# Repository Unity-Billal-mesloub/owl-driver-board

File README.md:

The OWL Driver Board is a solid-state relay HAT for the Raspberry Pi. It was
developed for use with the [Open Weed Locator](https://github.com/Unity-Agriculture/OpenWeedLocator) 
but is suitable for any high-power, industrial, automotive or agricultural application.

It allows a Raspberry Pi to drive either 4x or 16x 2A outputs in any 12V or 24V
system, with the solid state switching allowing PWM control, including for
dimming LED strips. Outputs can be placed in parallel for more power if needed.

It is able to tolerate high levels of electrical noise, reverse polarity, short
circuit conditions and over voltage. It also protects the Pi from all this
electrical nastiness and provides a filtered source of 5V @ 5A!

It's ideal for use safely driving LED strips, high power motors, relays and
solenoids from a Raspberry Pi.

The board aims to be difficult to misconfigure and hard to damage.
Self-resetting polyfuses on the input and outputs limit current, and
TVS+Schottky diodes provide reverse polarity protection, protection against
noise and inductive voltage spikes, and over-voltage protection. This
protection also extends to communication buses with the Raspberry Pi.

# Features

### Both models (4x and 16x output versions)

* Open Hardware, made in the UK: schematics and design files freely available.
* Working voltage 7-26V
* 4x or 16x fused outputs, each max. 2A, high-side switched
* 1x e-stop / global enable input
* Outputs can be driven in multiple ways, configurable by a header
* From Raspberry PI GPIOs
* Directly from external control, via wires to a header. Control inputs are tolerant up to 26V.
* Buck converter generates 5.1V @ 3A continuous / 5A burst to power the Raspberry Pi (Pi 5 compatible!)
* Input and outputs are fused, with protection against over-voltage, reverse polarity, and inductive spikes
* LED indication of blown fuses

### Additional features for the 4x output version only

* 1x fused input max. 7A
* Self-resetting input polyfuse
* Integrated PCA9685 PWM driver allows optional PWM control via I2C, compatible with Adafruit PCA9675 Python libraries
* Input and output connectors use high-quality Phoenix Contact screw terminals
* Version 2.4

### Additional features for the 16x output version only

* 3x fused inputs max. 10A each (connect all inputs in parallel for 30A total board input power)
* 10A mini-blade fuses on inputs
* Spare fuse holder
* Inputs and outputs use JST VH connectors
* Version 1.0

# Purchase a finished board

You can buy a finished board (4x or 16x output versions) via the following distributors:

 * [paradar.co.uk](https://paradar.co.uk/products/owl-driver-board-raspberry-pi-automotive-relay-hat)

# Changelog

## 16x v1.1

* Correctly connect the input connectors to the input fuses.
* Add 10k discharge resistors across each output, to reduce "ghost voltages"
  see when outputs are off, caused by leakage across the MOSFETs

## 16x v1.0

* Initial prototype of a 16-output version of the PCB. Note the Gerbers for
  this version have a bug - the input connectors are not attached to the fuse
  input, and a link must be manually soldered.

## 4x v2.5

* Add 10k discharge resistors across each output, to reduce "ghost voltages"
  see when outputs are off, caused by leakage across the MOSFETs
* Change screw terminals for Phoenix Contact part 1935161 (C3819953), replaces 1890963. #1935161 is 11mm in height (down from 13mm) which improves clearance
  in the enclosure.

## 4x v2.4

* Add an "output enable" terminal (J10) for use with an emergency stop switch.
  Outputs are enabled when the terminal is shorted; they are disabled when it
  is disconnected.

## 4x v2.3

* Improved Pi regulator efficiency (81% -> 87%) to reduce heat generated when
  driving a Raspberry Pi 5

## 4x v2.2

* Change out the switching buck regulator from a 2A max limit to a 5A model.
  Increase the regulation voltage from 5.0V -> 5.1V to drive a Raspberry Pi 5
  without undervoltage warnings.
* Add a LM73100 ideal diode on the Pi 5V output to ensure there is no backflow
  of current from the Pi into the board when powered off, and the Pi has a
  separate USB-C power supply.

## 4x v2.1

* Add a slot for the Raspberry Pi camera connector, to allow the ribbon cable
  to easily pass through the driver board.
* Remove stacking power connector to allow space for the cable slot. If
  stacking is required, board power inputs should be wired in parallel.
* Fix major error in v2.0 where MOSFET rotations were incorrect
* General manufacturability improvements (component polarity in silkscreen)

## 4x v2.0

* Significantly rework layout to allow space for instructions on the top. Move
  most components to the bottom layer.
* Change MOSFETs from TO-220 to a compact SMD footprint.
* Add indicator LED to each output and the power input.
* Switch to generic spring connectors that are PTH rather than SMD; the Wago
  SMD connectors did not hold up well in use.
* Change diodes from SMA to DO-123F to save space.
* Change most resistors from 0805 to 0603 to save space.

## 4x v1.0

Initial prototype.

# Schematic and layout

KiCanvas links:

 * [Schematic](https://kicanvas.org/?github=https%3A%2F%2Fgithub.com%2Fgeezacoleman%2Fowl-driver-board%2Fblob%2Fmain%2Fpcb%2Fowl-driver-board.kicad_sch)
 * [Layout](https://kicanvas.org/?github=https%3A%2F%2Fgithub.com%2Fgeezacoleman%2Fowl-driver-board%2Fblob%2Fmain%2Fpcb%2Fowl-driver-board.kicad_pcb)

# License

This open hardware project is Copyright (c) 2022 Guy Coleman and Patrick Coleman, and is released under an MIT license.

# Stacking

The HATs may be stacked and controlled with the PCA9685 by selecting different
I2C addresses for each board in the stack. In this configuation, the input power
terminals should be wired in parallel. Ensure that the wires used are rated for
sufficient current.

When stacked and in GPIO mode, turning on output #1 from the Raspberry Pi will
turn on all #1 outputs in the stack.

For individual control of all outputs in the stack
1. Set jumpers on header J6 to control outputs via the PCA9685 (the "PWM" setting).
1. Set SW1 to select a different address for each board in the stack.
1. Use the Adafruit PCA9685 Python library on the Raspberry Pi to communicate
   with each board via the chosen I2C addresses and control outputs
   individually.

Pi pin 22 (GPIO25) is connected to the PCA9685 Output Enable pin. Driving this
pin high on the Pi will disable all outputs in the stack (eg, for a software
emergency stop). It must be driven low for normal operation.

# Manufacturing

The project is set up for easy manufacture and assembly with JLCPCB, though it
will work with other suppliers too. All components should be available at
JLCPCB/LCSC and LCSC part numbers are included in KiKad fields for each part.

If you are having JLCPCB assemble the boards for you, you must manufacture in
panels (two boards per panel), as the board is too small for assembly alone. If
you will be assembling yourself, use pcb/gerbers/gb-owl-driver-board.zip for a single board.

1. Upload pcb/gerbers-panel-v2.4/gb-owl-driver-board-v2.4.zip to [JLCPCB's order tool](https://cart.jlcpcb.com/quote)
1. Configure the PCB manufacture settings to your requirements. Select "Confirm production file: Yes"
1. Select SMT assembly, and configure as follows: "Standard" assembly, "Both sides", and "Confirm production file". Click Confirm.
1. When prompted, upload the BOM (pcb/owl-driver-board_bom_jlc.csv) and Component Placement/CPL (pcb/owl-driver-board_cpl_jlc.csv) files.
1. Complete the SMT assembly wizard, aligning the parts to the board if necessary.

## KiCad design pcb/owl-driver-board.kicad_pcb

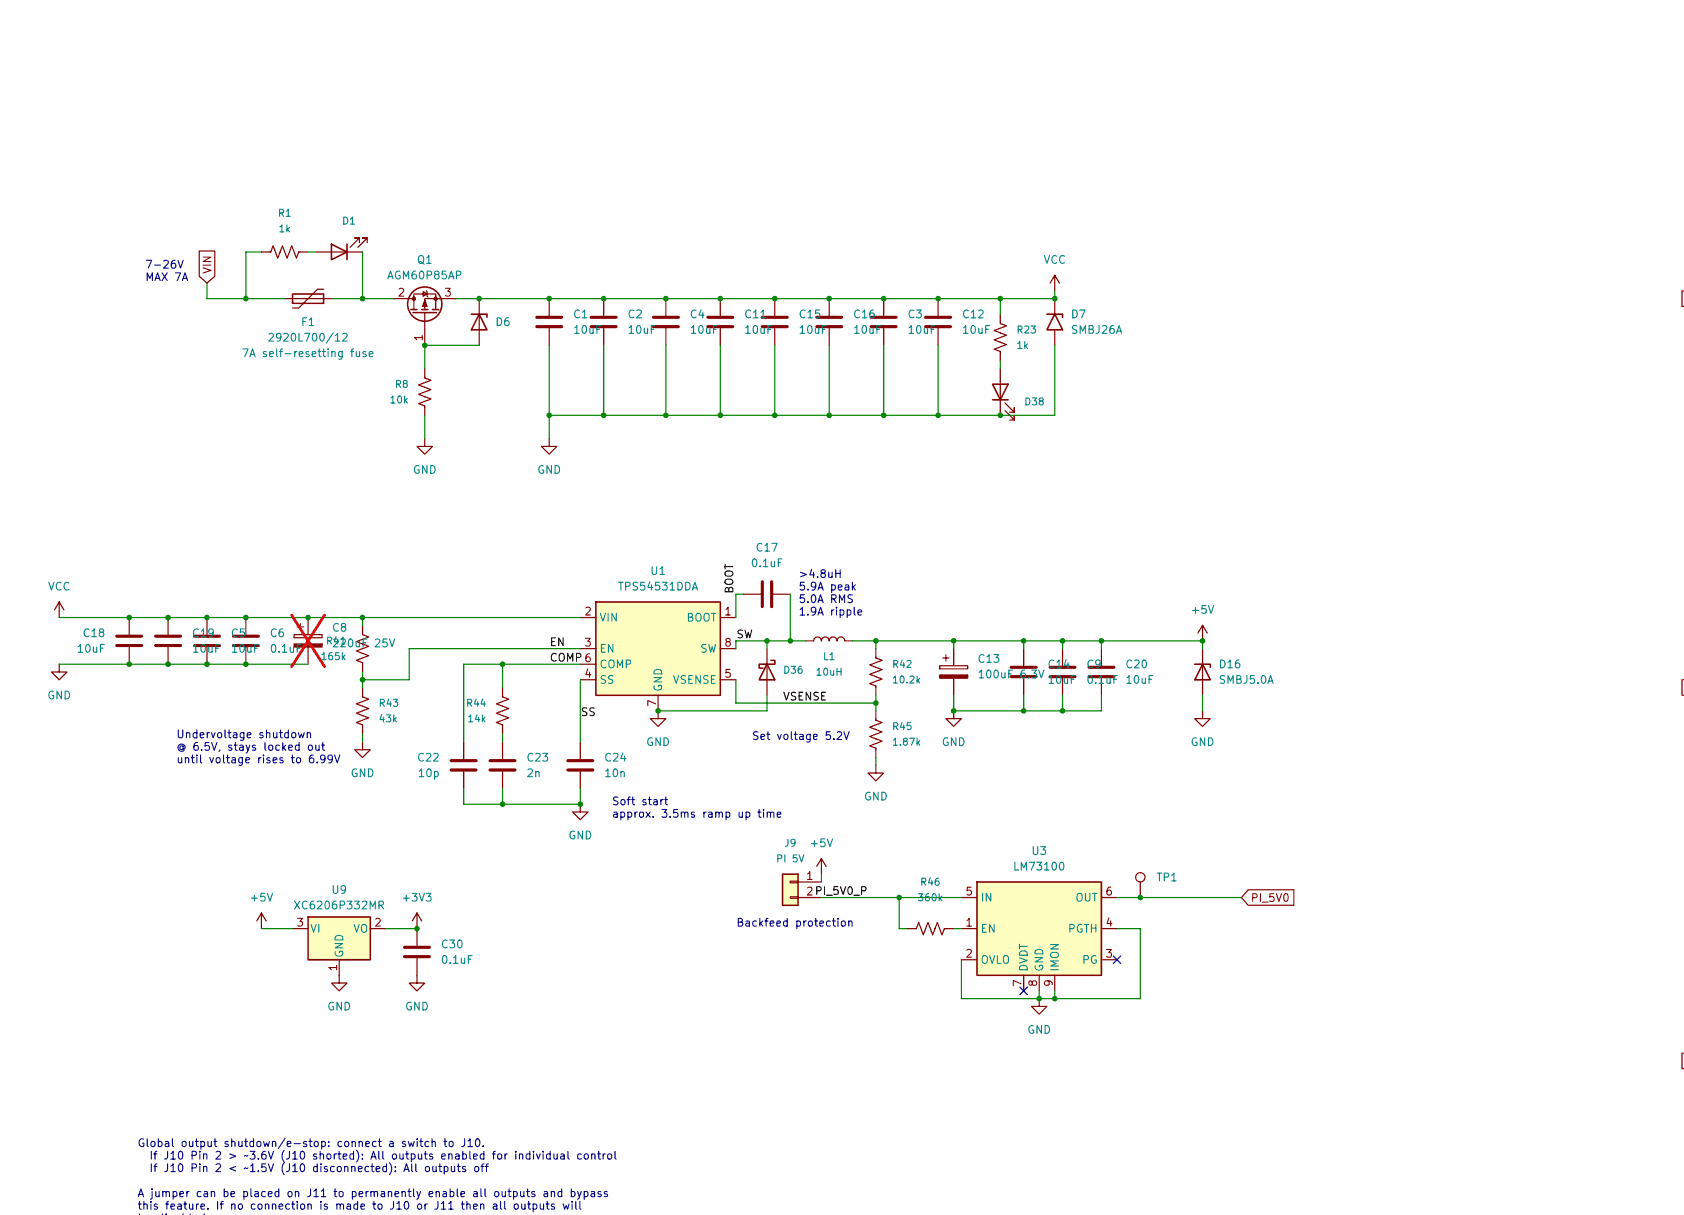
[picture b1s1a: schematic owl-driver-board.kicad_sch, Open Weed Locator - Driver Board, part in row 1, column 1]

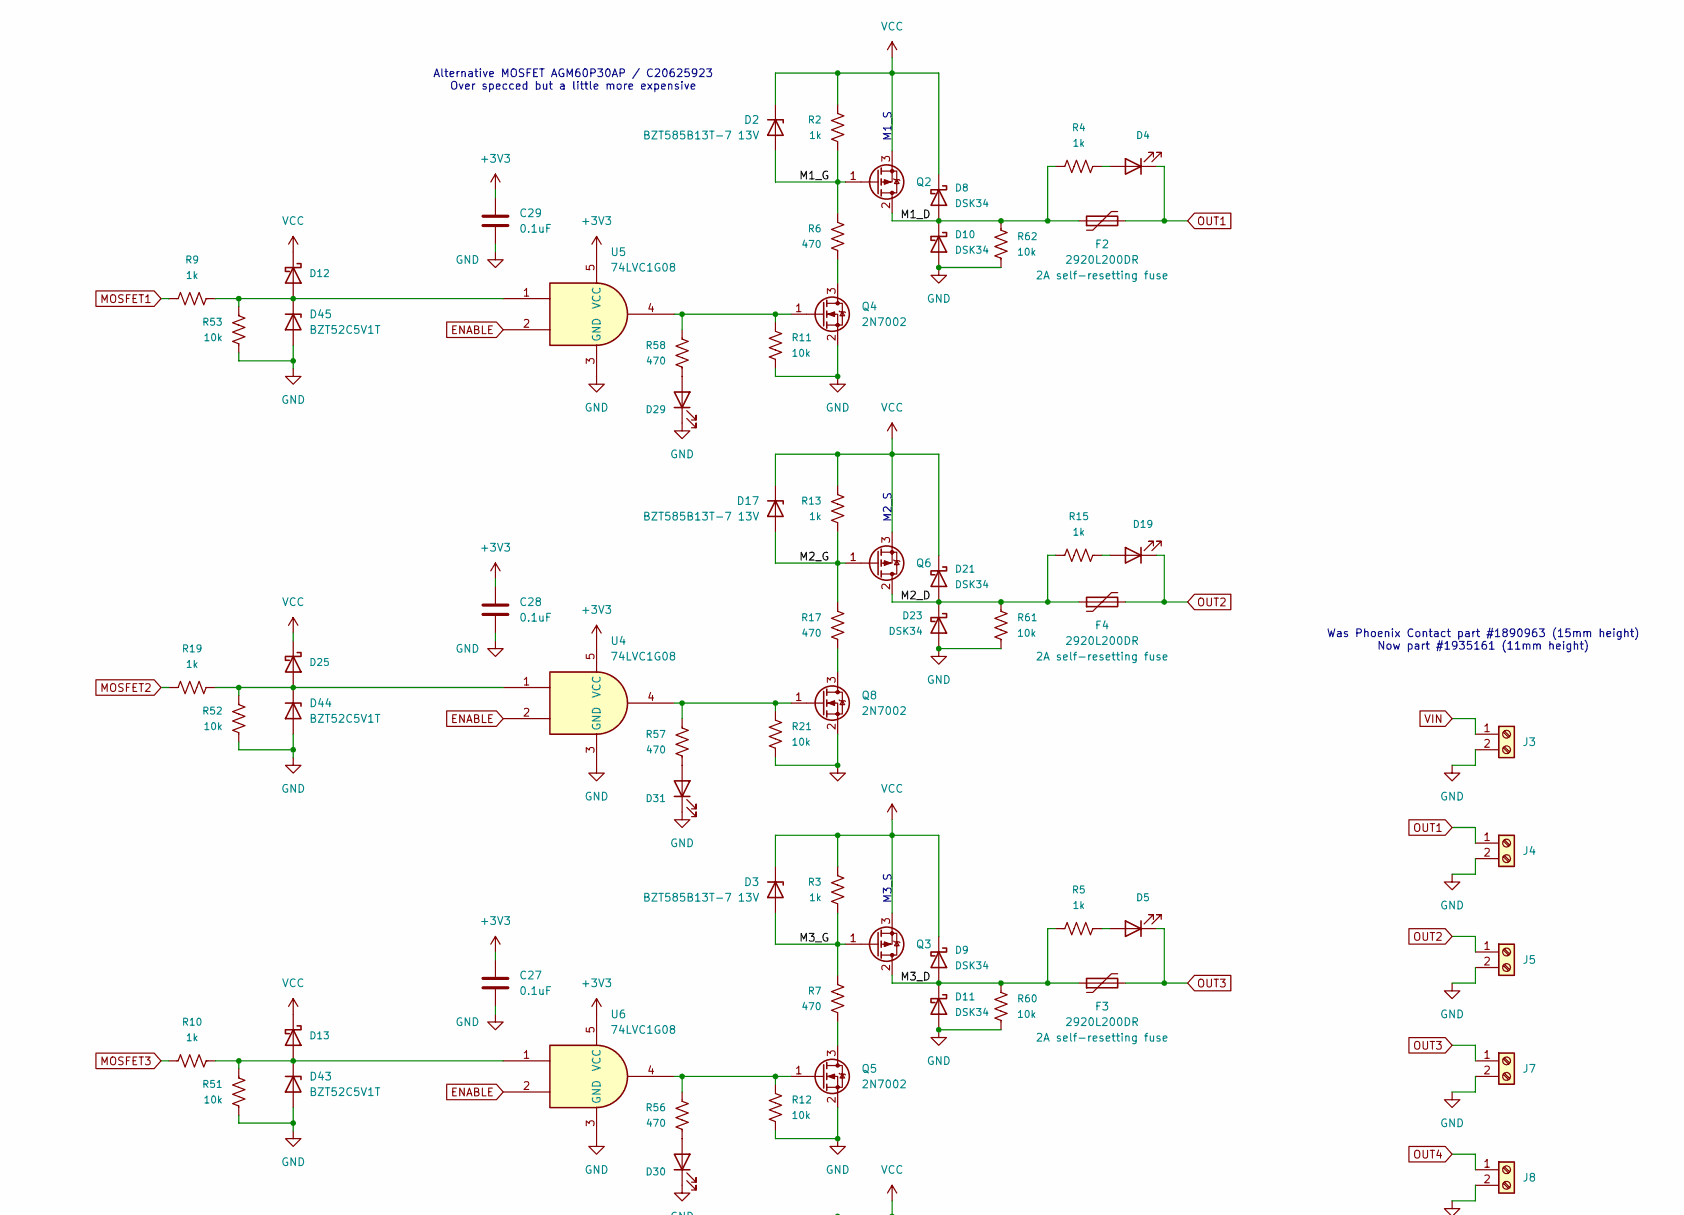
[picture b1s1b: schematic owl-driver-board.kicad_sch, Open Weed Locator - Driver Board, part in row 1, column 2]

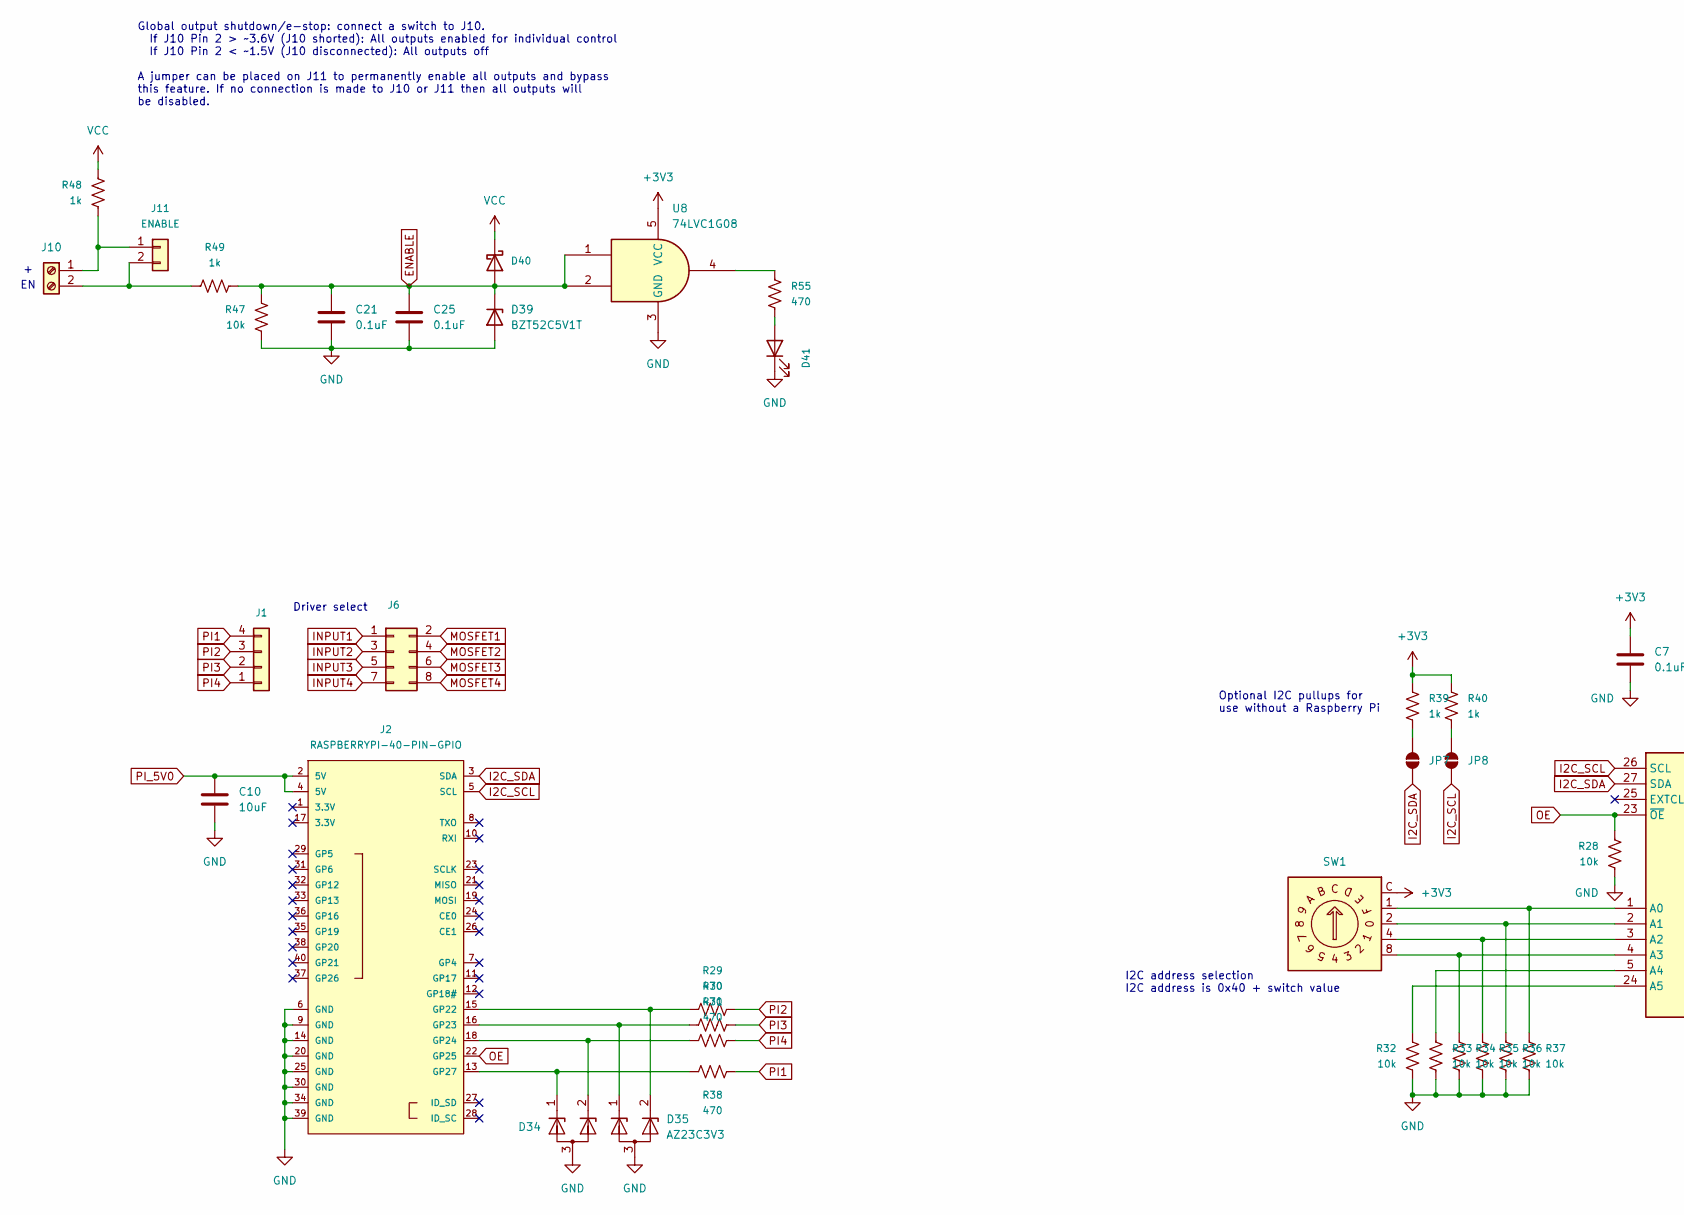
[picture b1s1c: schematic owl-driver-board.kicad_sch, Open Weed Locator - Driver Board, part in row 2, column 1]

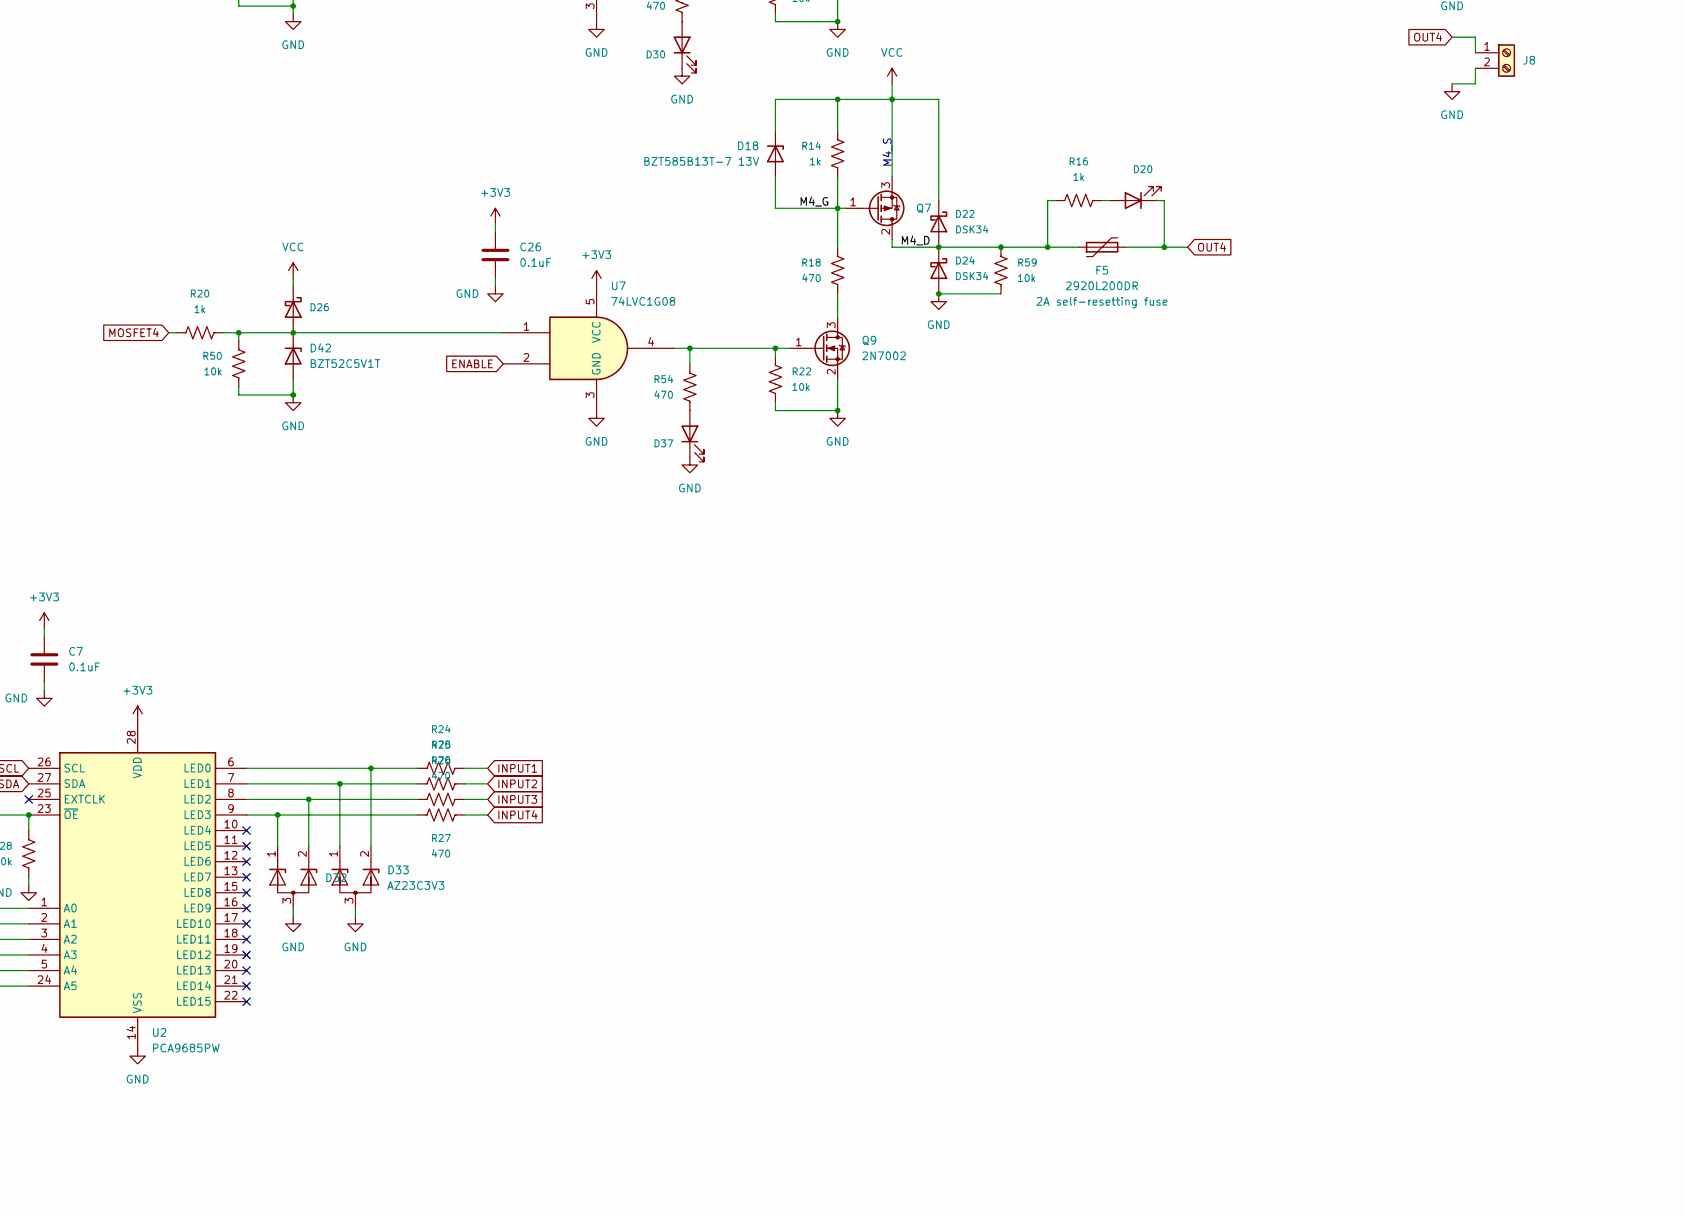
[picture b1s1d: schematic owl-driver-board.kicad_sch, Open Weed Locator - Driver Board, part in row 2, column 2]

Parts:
C1, C2, C3, C4, C5, C10, C11, C12, C14, C15, C16, C18, C19, C20: 10uF; C_1206_3216Metric_nosilk; Part 1206X106K500CT; LCSC C89835
C6, C7, C9, C17, C21, C25, C26, C27, C28, C29, C30: 0.1uF; C_0603_1608Metric_nosilk; LCSC C14663
C8: 220uF 25V; CP_Radial_D8.0mm_P3.50mm; LCSC C216322; not fitted
C13: 100uF 6.3V; CP_EIA-3528-21_Kemet-B; LCSC C16133
C22: 10p; C_0805_2012Metric; Part CC0805JRNPO9BN100; LCSC C107107
C23: 2n; C_0603_1608Metric_nosilk; Part GCM1885C1H202FA16J; LCSC C1870141
C24: 10n; C_0603_1608Metric_nosilk; Part GRM188R71H103KA01D; LCSC C77053
D1, D4, D5, D19, D20: SZYY0805R; LED_0805_2012Metric; LCSC C434431
D2, D3, D6, D17, D18: BZT585B13T-7 13V; D_SOD-523_silkpolarity; Part BZT585B13T-7; LCSC C460799
D7: SMBJ26A; D_SMB_silkpolarity; LCSC C315992
D8, D9, D10, D11, D12, D13, D21, D22, D23, D24, D25, D26, D40: DSK34; D_SOD-123F_silkpolarity; LCSC C727076
D16: SMBJ5.0A; D_SMB_silkpolarity; LCSC C83333
D29, D30, D31, D37, D38, D41: SZYY0805YG; LED_0805_2012Metric; LCSC C434435
D32, D33, D34, D35: AZ23C3V3; SOT-23_nosilk; LCSC C968007
D36: PDS1040L-13; D_PowerDI-5; Part PDS1040L-13; LCSC C154714
D39, D42, D43, D44, D45: BZT52C5V1T; D_SOD-523_silkpolarity; LCSC C2987034
F1: 2920L700/12; Fuse_2920_7451Metric_nosilk; LCSC C207092
F2, F3, F4, F5: 2920L200DR; Fuse_2920_7451Metric_nosilk; LCSC C207087
J1: CONN_04; 1X04_NO_SILK; LCSC C358686
J2: RASPBERRYPI-40-PIN-GPIO; Pin_Header_Straight_2x20; LCSC C35165
J3, J4, J5, J7, J8, J10: 1935161; TerminalBlock_Phoenix_PT-1,5-2-5.0-H_1x02_P5.00mm_Horizontal; Part 1935161; LCSC C3819953
J6: CONN_04X2; 2X4; LCSC C358693
J9: PI 5V; PinHeader_1x02_P2.54mm_Vertical_nosilk; LCSC C358684
J11: ENABLE; PinHeader_1x02_P2.54mm_Vertical_nosilk; LCSC C358684
JP7, JP8: A0; SolderJumper-2_P1.3mm_Open_RoundedPad1.0x1.5mm_nosilk
L1: 10uH; L_10.4x10.4_H4.8; Part CXP1050-100M-AG(10uh); LCSC C7461391
Q1, Q2, Q3, Q6, Q7: AGM60P85AP; PDFN-8-3.3x3.3; LCSC C17701049
Q4, Q5, Q8, Q9: 2N7002; SOT-23_nosilk; LCSC C8545
R1, R2, R3, R4, R5, R9, R10, R13, R14, R15, R16, R19, R20, R23, R39, R40, R48, R49: 1k; R_0603_1608Metric; LCSC C21190
R6, R7, R17, R18, R24, R25, R26, R27, R29, R30, R31, R38, R54, R55, R56, R57, R58: 470; R_0603_1608Metric; LCSC C25241
R8, R11, R12, R21, R22, R28, R32, R33, R34, R35, R36, R37, R47, R50, R51, R52, R53, R59, R60, R61, R62: 10k; R_0603_1608Metric; LCSC C15401
R41: 165k; R_0603_1608Metric; Part 0603WAF1653T5E; LCSC C22816
R42: 10.2k; R_0603_1608Metric; Part 0603WAF1022T5E; LCSC C22772
R43: 43k; R_0603_1608Metric; Part 0603WAF4302T5E; LCSC C23172
R44: 14k; R_0603_1608Metric; Part 0603WAF1402T5E; LCSC C22803
R45: 1.87k; R_0603_1608Metric; Part 0603WAF1871T5E; LCSC C22850
R46: 360k; R_0603_1608Metric; Part 0603WAF3603T5E; LCSC C23146
SW1: SW_Coded_SH-7050; Diptronics-Rotary-Switch-R7M3-16RA-V; Part R7M3-16RA-V-T/R; LCSC C501563
TP1: TestPoint; TestPoint_Pad_D1.5mm_NoSilk
U1: TPS54531DDA; Texas_R-PDSO-G8_EP2.95x4.9mm_Mask2.4x3.1mm_ThermalVias; Part TPS54531DDAR; LCSC C50605
U2: PCA9685PW; TSSOP-28_4.4x9.7mm_P0.65mm; LCSC C2678753
U3: LM73100; LM73100-QFN10; Part LM73100RPWR; LCSC C3210761
U4, U5, U6, U7, U8: 74LVC1G08; SOT-353_SC-70-5; Part 74LVC1G08GW,125; LCSC C12512
U9: XC6206P332MR; SOT-23; Part XC6206P332MR; LCSC C5148692

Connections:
+3V3: C7.1, C26.1, C27.1, C28.1, C29.1, C30.1, R39.2, R40.2, SW1.C, U2.28 (VDD), U4.5 (VCC), U5.5 (VCC), U6.5 (VCC), U7.5 (VCC), U8.5 (VCC), U9.2 (VO)
+5V: C9.1, C13.1, C14.1, C20.1, D16.1 (K), J9.1, L1.2, R42.2, U9.3 (VI)
/BOOT: C17.1, U1.1 (BOOT)
/COMP: C22.1, R44.1, U1.6 (COMP)
/EN: R41.1, R43.2, U1.3 (EN)
/M1_D: D8.2 (A), D10.1 (K), F2.1, Q2.2 (D), R4.2, R62.2
/M1_G: D2.2 (A), Q2.1 (G), R2.1, R6.2
/M2_D: D21.2 (A), D23.1 (K), F4.1, Q6.2 (D), R15.2, R61.2
/M2_G: D17.2 (A), Q6.1 (G), R13.1, R17.2
/M3_D: D9.2 (A), D11.1 (K), F3.1, Q3.2 (D), R5.2, R60.2
/M3_G: D3.2 (A), Q3.1 (G), R3.1, R7.2
/M4_D: D22.2 (A), D24.1 (K), F5.1, Q7.2 (D), R16.1, R59.2
/M4_G: D18.2 (A), Q7.1 (G), R14.1, R18.2
/PI_5V0_P: J9.2, R46.2, U3.5 (IN)
/SS: C24.1, U1.4 (SS)
/SW: C17.2, D36.1 (K), L1.1, U1.8 (SW)
/VSENSE: R42.1, R45.2, U1.5 (VSENSE)
ENABLE: C21.1, C25.1, D39.1 (K), D40.2 (A), R47.1, R49.2, U4.2, U5.2, U6.2, U7.2, U8.1, U8.2
GND: C1.2, C2.2, C3.2, C4.2, C5.2, C6.2, C7.2, C8.2, C9.2, C10.2, C11.2, C12.2, C13.2, C14.2, C15.2, C16.2, C18.2, C19.2, C20.2, C21.2, C22.2, C23.2, C24.2, C25.2, C26.2, C27.2, C28.2, C29.2, C30.2, D7.2 (A2), D10.2 (A), D11.2 (A), D16.2 (A), D23.2 (A), D24.2 (A), D29.1 (K), D30.1 (K), D31.1 (K), D32.3 (A), D33.3 (A), D34.3 (A), D35.3 (A), D36.2 (A), D37.1 (K), D38.1 (K), D39.2 (A), D41.1 (K), D42.2 (A), D43.2 (A), D44.2 (A), D45.2 (A), J2.6 (GND), J2.9 (GND), J2.14 (GND), J2.20 (GND), J2.25 (GND), J2.30 (GND), J2.34 (GND), J2.39 (GND), J3.2, J4.2, J5.2, J7.2, J8.2, Q4.2 (S), Q5.2 (S), Q8.2 (S), Q9.2 (S), R8.1, R11.1, R12.1, R21.1, R22.1, R28.1, R32.1, R33.1, R34.1, R35.1, R36.1, R37.1, R43.1, R45.1, R47.2, R50.1, R51.1, R52.1, R53.1, R59.1, R60.1, R61.1, R62.1, U1.7 (GND), U1.9 (GND), U2.14 (VSS), U3.2 (OVLO), U3.4 (PGTH), U3.8 (GND), U3.9 (IMON), U4.3 (GND), U5.3 (GND), U6.3 (GND), U7.3 (GND), U8.3 (GND), U9.1 (GND)
I2C_SCL: J2.5 (SCL), JP8.1 (A), U2.26 (SCL)
I2C_SDA: J2.3 (SDA), JP7.1 (A), U2.27 (SDA)
INPUT1: J6.1, R24.2
INPUT2: J6.3, R25.2
INPUT3: J6.5, R26.2
INPUT4: J6.7, R27.2
MOSFET1: J6.2, R9.2
MOSFET2: J6.4, R19.2
MOSFET3: J6.6, R10.2
MOSFET4: J6.8, R20.2
unnamed: C23.1, R44.2
unnamed: D1.2 (A), R1.1
unnamed: D1.1 (K), F1.2, Q1.2 (D)
unnamed: D4.2 (A), R4.1
unnamed: D5.2 (A), R5.1
unnamed: D6.2 (A), Q1.1 (G), R8.2
unnamed: D12.2 (A), D45.1 (K), R9.1, R53.2, U5.1
unnamed: D13.2 (A), D43.1 (K), R10.1, R51.2, U6.1
unnamed: D19.2 (A), R15.1
unnamed: D20.2 (A), R16.2
unnamed: D25.2 (A), D44.1 (K), R19.1, R52.2, U4.1
unnamed: D26.2 (A), D42.1 (K), R20.1, R50.2, U7.1
unnamed: D29.2 (A), R58.1
unnamed: D30.2 (A), R56.1
unnamed: D31.2 (A), R57.1
unnamed: D37.2 (A), R54.1
unnamed: D38.2 (A), R23.1
unnamed: D41.2 (A), R55.1
unnamed: D35.2 (K), J2.15 (GP22), R29.1
unnamed: D35.1 (K), J2.16 (GP23), R30.1
unnamed: D34.2 (K), J2.18 (GP24), R31.1
unnamed: D34.1 (K), J2.13 (GP27), R38.1
unnamed: J10.1, J11.1, R48.2
unnamed: J10.2, J11.2, R49.1
unnamed: JP7.2 (B), R39.1
unnamed: JP8.2 (B), R40.1
unnamed: Q4.3 (D), R6.1
unnamed: Q4.1 (G), R11.2, R58.2, U5.4
unnamed: Q5.3 (D), R7.1
unnamed: Q5.1 (G), R12.2, R56.2, U6.4
unnamed: Q8.3 (D), R17.1
unnamed: Q8.1 (G), R21.2, R57.2, U4.4
unnamed: Q9.3 (D), R18.1
unnamed: Q9.1 (G), R22.2, R54.2, U7.4
unnamed: R55.2, U8.4
unnamed: R37.2, SW1.1, U2.1 (A0)
unnamed: R36.2, SW1.2, U2.2 (A1)
unnamed: R35.2, SW1.4, U2.3 (A2)
unnamed: R34.2, SW1.8, U2.4 (A3)
unnamed: R33.2, U2.5 (A4)
unnamed: R32.2, U2.24 (A5)
unnamed: D33.2 (K), R24.1, U2.6 (LED0)
unnamed: D33.1 (K), R25.1, U2.7 (LED1)
unnamed: D32.2 (K), R26.1, U2.8 (LED2)
unnamed: D32.1 (K), R27.1, U2.9 (LED3)
unnamed: R46.1, U3.1 (EN)
OE: J2.22 (GP25), R28.2, U2.23 (~OE)
OUT1: D4.1 (K), F2.2, J4.1
OUT2: D19.1 (K), F4.2, J5.1
OUT3: D5.1 (K), F3.2, J7.1
OUT4: D20.1 (K), F5.2, J8.1
PI1: J1.4, R38.2
PI2: J1.3, R29.2
PI3: J1.2, R30.2
PI4: J1.1, R31.2
PI_5V0: C10.1, J2.2 (5V), J2.4 (5V), TP1.1, U3.6 (OUT)
VCC: C1.1, C2.1, C3.1, C4.1, C5.1, C6.1, C8.1, C11.1, C12.1, C15.1, C16.1, C18.1, C19.1, D2.1 (K), D3.1 (K), D6.1 (K), D7.1 (A1), D8.1 (K), D9.1 (K), D12.1 (K), D13.1 (K), D17.1 (K), D18.1 (K), D21.1 (K), D22.1 (K), D25.1 (K), D26.1 (K), D40.1 (K), Q1.3 (S), Q2.3 (S), Q3.3 (S), Q6.3 (S), Q7.3 (S), R2.2, R3.2, R13.2, R14.2, R23.2, R41.2, R48.1, U1.2 (VIN)
VIN: F1.1, J3.1, R1.2

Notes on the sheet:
I2C address selection I2C address is 0x40 + switch value
M2_S
Undervoltage shutdown @ 6.5V, stays locked out until voltage rises to 6.99V
Backfeed protection
M4_S
Driver select
Optional I2C pullups for use without a Raspberry Pi
Soft start approx. 3.5ms ramp up time
>4.8uH 5.9A peak 5.0A RMS 1.9A ripple
Set voltage 5.2V
Alternative MOSFET AGM60P30AP / C20625923 Over specced but a little more expensive
Global output shutdown/e-stop: connect a switch to J10. If J10 Pin 2 > ~3.6V (J10 shorted): All outputs enabled for individual control If J10 Pin 2 < ~1.5V (J10 disconnected): All outputs off A jumper can be placed on J11 to permanently enable all outputs and bypass this feature. If no connection i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
M3_S
M1_S
7-26V MAX 7A
Was Phoenix Contact part #1890963 (15mm height) Now part #1935161 (11mm height)

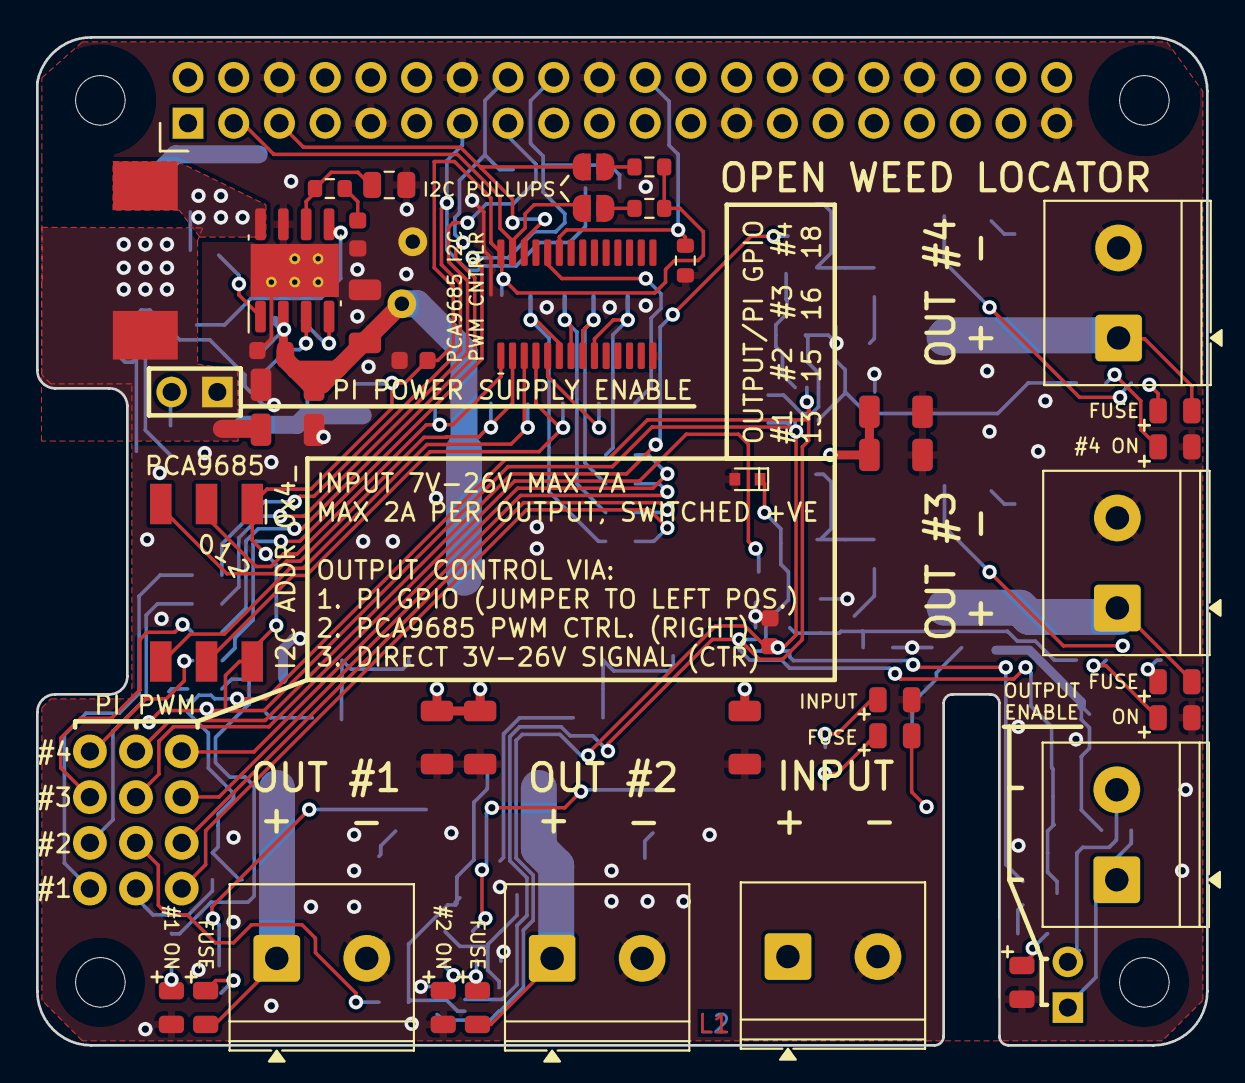
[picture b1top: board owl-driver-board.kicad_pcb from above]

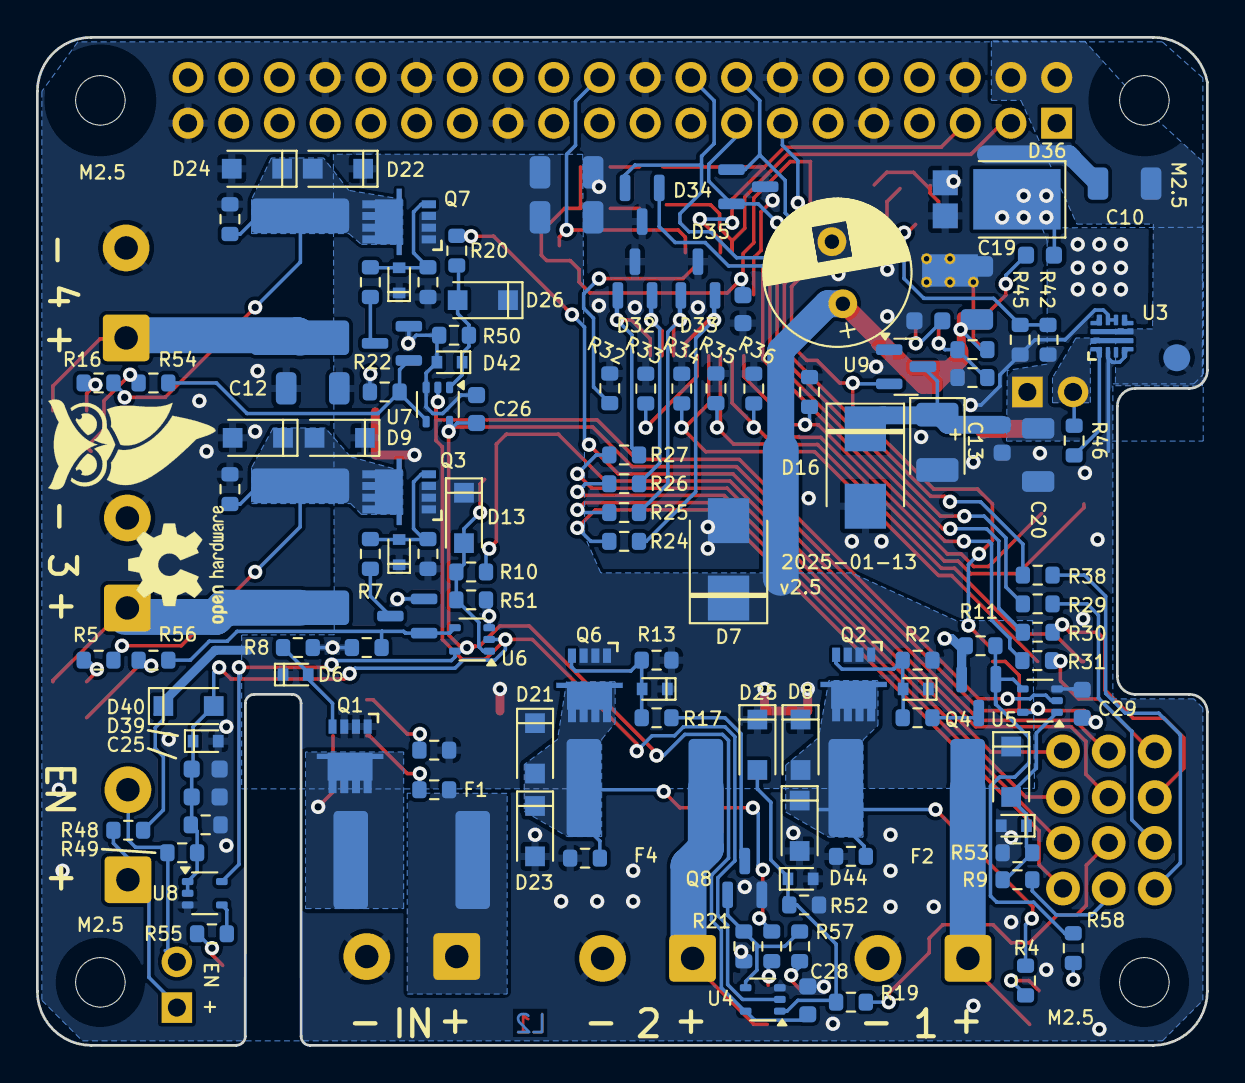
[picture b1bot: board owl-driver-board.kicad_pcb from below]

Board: 2 copper layers, 65.0 x 56.0 mm, 181 parts (127 on the bottom side), 87 nets.

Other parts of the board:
LOGO1: OSHW-Logo2_7.3x6mm_SilkScreen
PI1, PI2, PI3, PI4: RPi_Hat_Mounting_Hole
TAB1, TAB2, TAB3, TAB4: Tab

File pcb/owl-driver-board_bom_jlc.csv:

"Comment","Designator","Footprint","LCSC Part Number"
"10uF","C1,C2,C3,C4,C5,C10,C11,C12,C14,C15,C16,C18,C19,C20","C_1206_3216Metric_nosilk","C89835"
"0.1uF","C6,C7,C9,C17,C21,C25,C26,C27,C28,C29,C30","C_0603_1608Metric_nosilk","C14663"
"100uF 6.3V","C13","CP_EIA-3528-21_Kemet-B","C16133"
"10p","C22","C_0805_2012Metric","C107107"
"2n","C23","C_0603_1608Metric_nosilk","C1870141"
"10n","C24","C_0603_1608Metric_nosilk","C77053"
"SZYY0805R","D1,D4,D5,D19,D20","LED_0805_2012Metric","C434431"
"BZT585B13T-7 13V","D2,D3,D6,D17,D18","D_SOD-523_silkpolarity","C460799"
"SMBJ26A","D7","D_SMB_silkpolarity","C315992"
"DSK34","D8,D9,D10,D11,D12,D13,D21,D22,D23,D24,D25,D26,D40","D_SOD-123F_silkpolarity","C727076"
"SMBJ5.0A","D16","D_SMB_silkpolarity","C83333"
"SZYY0805YG","D29,D30,D31,D37,D38,D41","LED_0805_2012Metric","C434435"
"AZ23C3V3","D32,D33,D34,D35","SOT-23_nosilk","C968007"
"PDS1040L-13","D36","D_PowerDI-5","C154714"
"BZT52C5V1T","D39,D42,D43,D44,D45","D_SOD-523_silkpolarity","C2987034"
"2920L700/12","F1","Fuse_2920_7451Metric_nosilk","C207092"
"2920L200DR","F2,F3,F4,F5","Fuse_2920_7451Metric_nosilk","C207087"
"CONN_04","J1","1X04_NO_SILK","C358686"
"RASPBERRYPI-40-PIN-GPIO","J2","Pin_Header_Straight_2x20","C35165"
"1935161","J3,J4,J5,J7,J8,J10","TerminalBlock_Phoenix_PT-1,5-2-5.0-H_1x02_P5.00mm_Horizontal","C3819953"
"CONN_04X2","J6","2X4","C358693"
"PI 5V","J9","PinHeader_1x02_P2.54mm_Vertical_nosilk","C358684"
"ENABLE","J11","PinHeader_1x02_P2.54mm_Vertical_nosilk","C358684"
"10uH","L1","L_10.4x10.4_H4.8","C7461391"
"AGM60P85AP","Q1,Q2,Q3,Q6,Q7","PDFN-8-3.3x3.3","C17701049"
"2N7002","Q4,Q5,Q8,Q9","SOT-23_nosilk","C8545"
"1k","R1,R2,R3,R4,R5,R9,R10,R13,R14,R15,R16,R19,R20,R23,R39,R40,R48,R49","R_0603_1608Metric","C21190"
"470","R6,R7,R17,R18,R24,R25,R26,R27,R29,R30,R31,R38,R54,R55,R56,R57,R58","R_0603_1608Metric","C25241"
"10k","R8,R11,R12,R21,R22,R28,R32,R33,R34,R35,R36,R37,R47,R50,R51,R52,R53,R59,R60,R61,R62","R_0603_1608Metric","C15401"
"165k","R41","R_0603_1608Metric","C22816"
"10.2k","R42","R_0603_1608Metric","C22772"
"43k","R43","R_0603_1608Metric","C23172"
"14k","R44","R_0603_1608Metric","C22803"
"1.87k","R45","R_0603_1608Metric","C22850"
"360k","R46","R_0603_1608Metric","C23146"
"SW_Coded_SH-7050","SW1","Diptronics-Rotary-Switch-R7M3-16RA-V","C501563"
"TPS54531DDA","U1","Texas_R-PDSO-G8_EP2.95x4.9mm_Mask2.4x3.1mm_ThermalVias","C50605"
"PCA9685PW","U2","TSSOP-28_4.4x9.7mm_P0.65mm","C2678753"
"LM73100","U3","LM73100-QFN10","C3210761"
"74LVC1G08","U4,U5,U6,U7,U8","SOT-353_SC-70-5","C12512"
"XC6206P332MR","U9","SOT-23","C5148692"

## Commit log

2026-01-13 add 16-way board v1.1, with additional discharge resistor across outputs
2026-01-13 4-way board, revision v2.5
    Bump the revision with some small tweaks -
    - Lower profile Phoenix Contact screw terminals - replace 1890963 with 1935161 (C3819953)
    - 10k discharge resistor across all outputs to reduce ghost voltages
    - Format updates for KiCad 9
